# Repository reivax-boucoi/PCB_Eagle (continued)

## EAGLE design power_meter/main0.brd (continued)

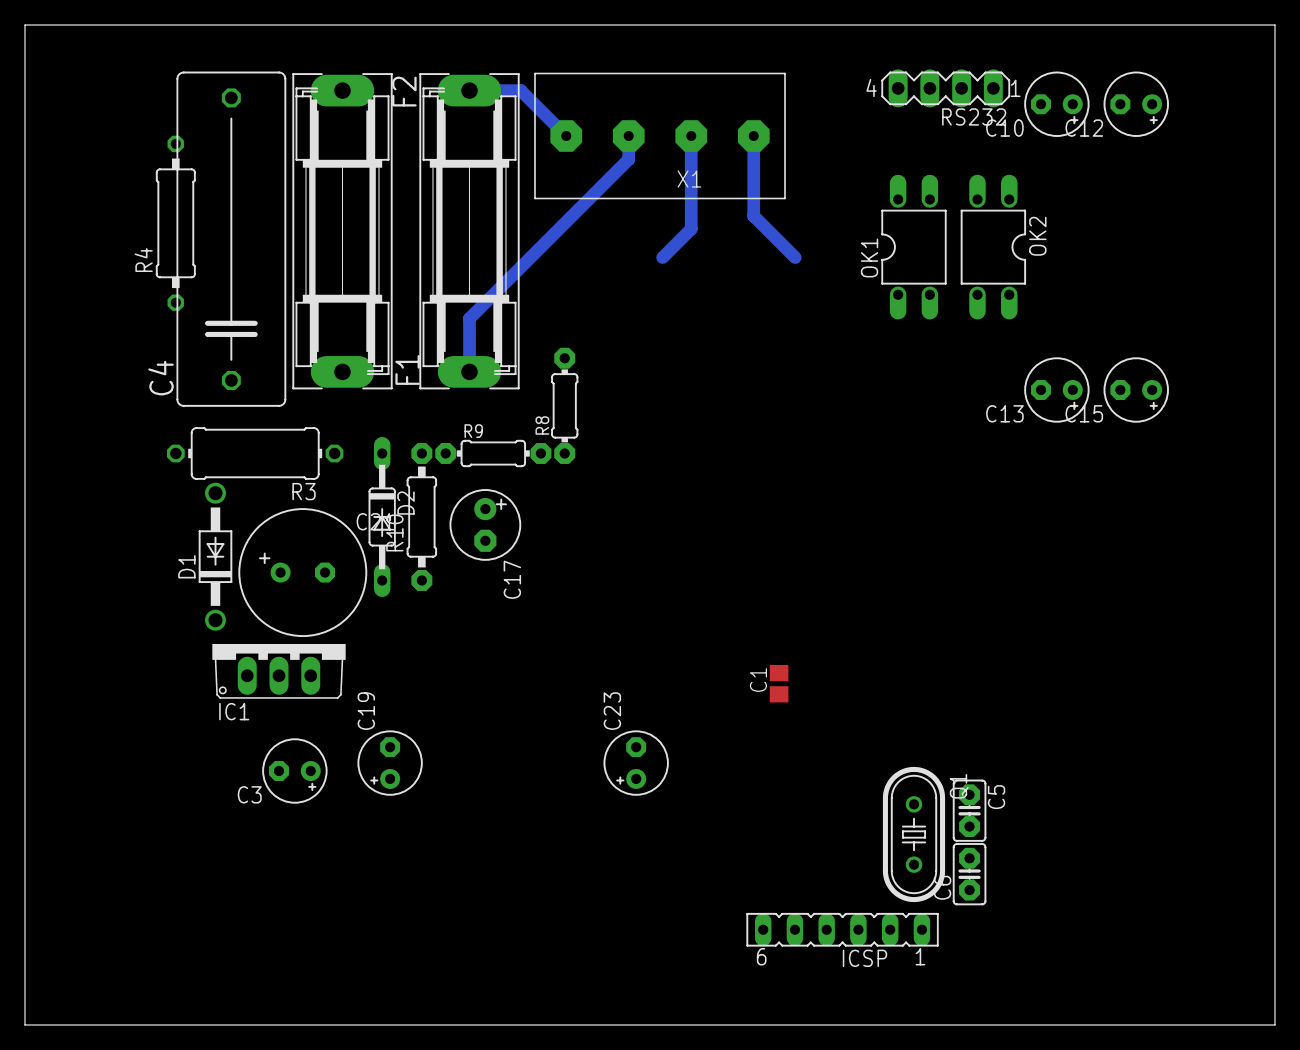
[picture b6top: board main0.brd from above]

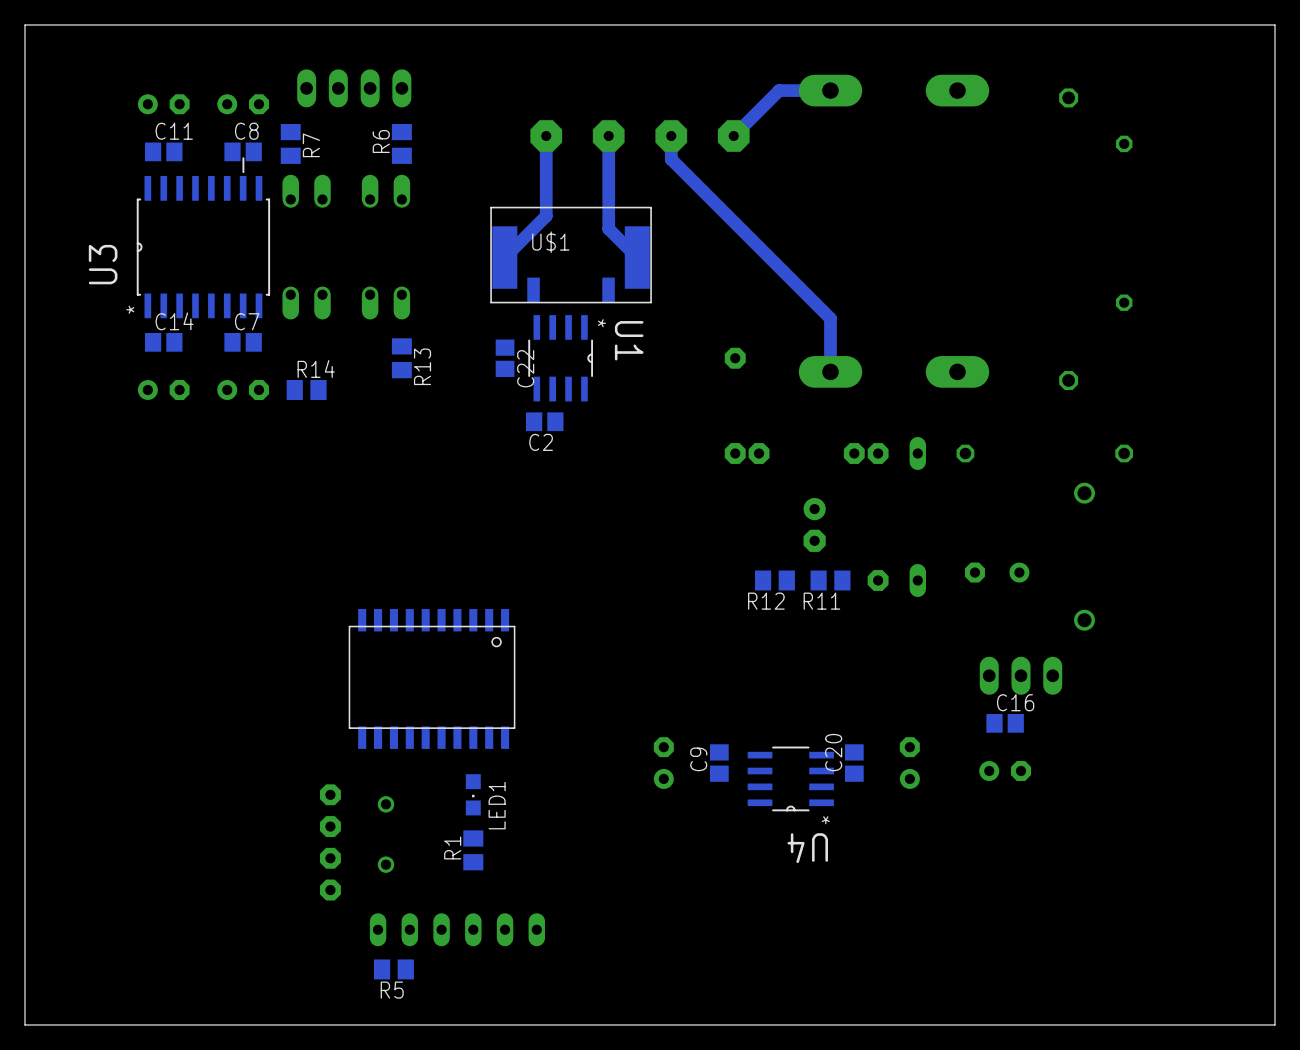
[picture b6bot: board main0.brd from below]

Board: 2 copper layers, 100.0 x 80.0 mm, 52 parts (23 on the bottom side), 32 nets.

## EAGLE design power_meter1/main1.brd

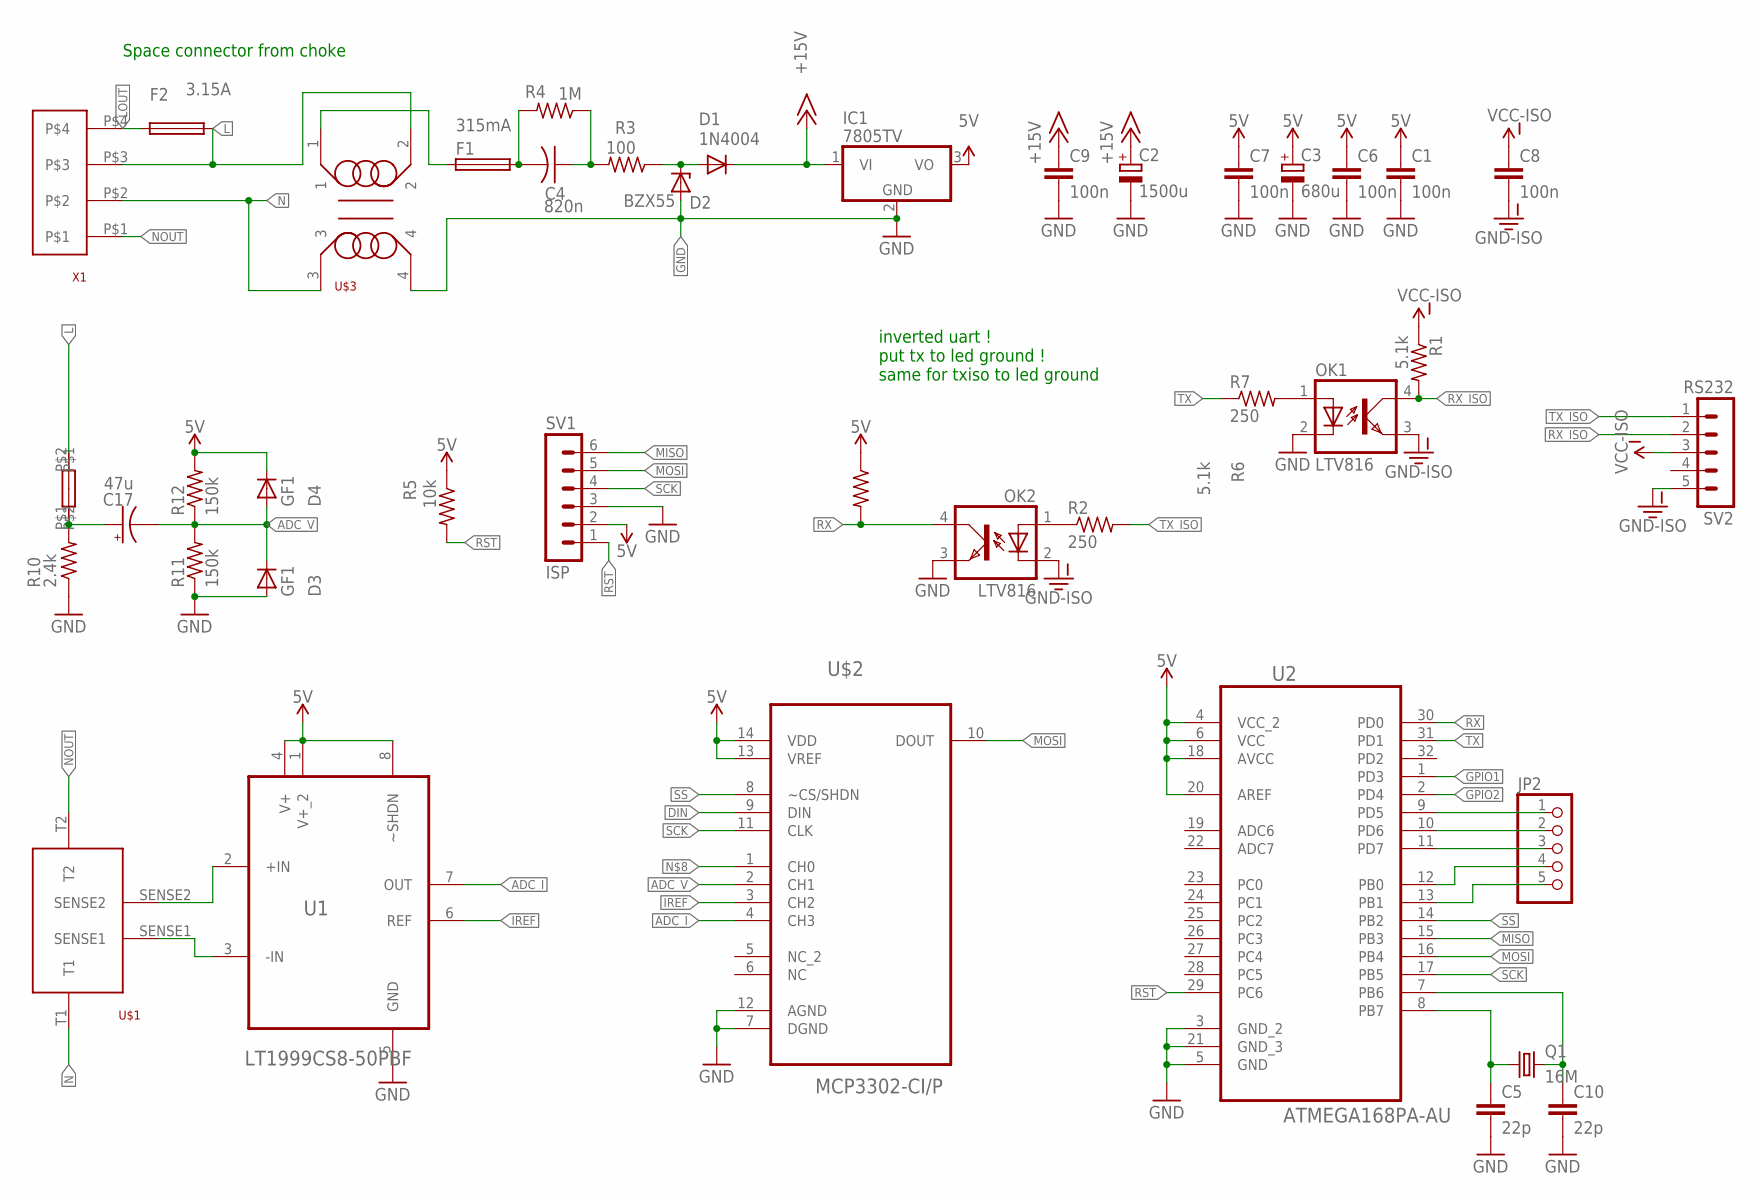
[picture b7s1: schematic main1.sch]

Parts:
C1, C6, C7, C9: 100n; C0603K
C2: 1500u; E5-10,5
C3: 680u; E3,5-8
C4: 820n; C225-087X268
C5, C10: 22p; C0603
C8: 100n; C0603
C17: 47u; E5-6
D1: 1N4004; DO41-10
D2: BZX55; DO35Z10
D3, D4: GF1; SMA-DO214AC
F1: 315mA; SH22,5
F2: 3.15A; SH22,5
IC1: 7805TV; TO220V
JP2: PINHD-1X5; 1X05
OK1, OK2: LTV816; DIL04
Q1: 16M; HC49U-V
R1: 5.1k; M0805
R2: 250; M0805
R3: 100; 0411/15
R4: 1M; 0617/17
R5: 10k; M0805
R6: 5.1k; R0603
R7: 250; R0603
R10: 2.4k; 0617/17
R11, R12: 150k; M0805
R13: 150k180k; RESISTOR_LONG
SV1: ISP; MA06-1
SV2: RS232; MA05-1
U1: LT1999CS8-50PBF; SOIC127P600X175-8N
U2: ATMEGA168PA-AU; QFP80P900X900X120-32N
U$1: CSR2TTE30L0F
U$2: MCP3302-CI/P; DIP254P762X533-14
U$3: B302L_CM_CHOKE
X1: SCREWTERM_5MM_4WAY

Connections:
5V: C1.1, C3.+, C6.1, C7.1, D4.K (C), IC1.3 (VO), R5.1, R6.1, R12.2, SV1.2, U1.1 (V+_2), U1.4 (V+), U1.8 (~SHDN), U2.4 (VCC_2), U2.6 (VCC), U2.18 (AVCC), U2.20 (AREF), U$2.13 (VREF), U$2.14 (VDD)
+15V: C2.+, C9.1, D1.C, IC1.1 (VI)
ADC_I: U1.7 (OUT), U$2.4 (CH3)
ADC_V: C17.-, D3.K (C), D4.A, R11.2, R12.1, U$2.2 (CH1)
DIN: U$2.9 (DIN)
GND: C1.2, C2.-, C3.-, C5.2, C6.2, C7.2, C9.2, C10.2, D2.A, D3.A, IC1.2 (GND), OK1.2 (C), OK2.3 (EMIT), R10.1, R11.1, SV1.3, U1.5 (GND), U2.3 (GND_2), U2.5 (GND), U2.21 (GND_3), U$2.7 (DGND), U$2.12 (AGND), U$3.4
GND-ISO: C8.2, OK1.3 (EMIT), OK2.2 (C), SV2.5
GPIO1: U2.1 (PD3)
GPIO2: U2.2 (PD4)
IREF: U1.6 (REF), U$2.3 (CH2)
L: F2.2, R13.P$2, U$3.2, X1.P$3
LOUT: F2.1, X1.P$4
MISO: SV1.6, U2.15 (PB3)
MOSI: SV1.5, U2.16 (PB4), U$2.10 (DOUT)
N: U$1.T1, U$3.3, X1.P$2
unnamed: C4.1, R3.2, R4.1
unnamed: C4.2, F1.2, R4.2
unnamed: D1.A, D2.C, R3.1
unnamed: U1.2 (+IN), U$1.SENSE2
unnamed: U1.3 (-IN), U$1.SENSE1
unnamed: F1.1, U$3.1
unnamed: OK1.1 (A), R7.2
unnamed: C5.1, Q1.1, U2.8 (PB7)
unnamed: C10.1, Q1.2, U2.7 (PB6)
unnamed: OK2.1 (A), R2.1
unnamed: JP2.1, U2.9 (PD5)
unnamed: JP2.2, U2.10 (PD6)
unnamed: JP2.3, U2.11 (PD7)
unnamed: JP2.4, U2.12 (PB0)
unnamed: JP2.5, U2.13 (PB1)
unnamed: C17.+, R10.2, R13.P$1
NOUT: U$1.T2, X1.P$1
RST: R5.2, SV1.1, U2.29 (PC6)
RX: OK2.4 (COL), R6.2, U2.30 (PD0)
RX_ISO: OK1.4 (COL), R1.2, SV2.2
SCK: SV1.4, U2.17 (PB5), U$2.11 (CLK)
SS: U2.14 (PB2), U$2.8 (~CS/SHDN)
TX: R7.1, U2.31 (PD1)
TX_ISO: R2.2, SV2.1
VCC-ISO: C8.1, R1.1, SV2.3

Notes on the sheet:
Space connector from choke
inverted uart ! put tx to led ground ! same for txiso to led ground

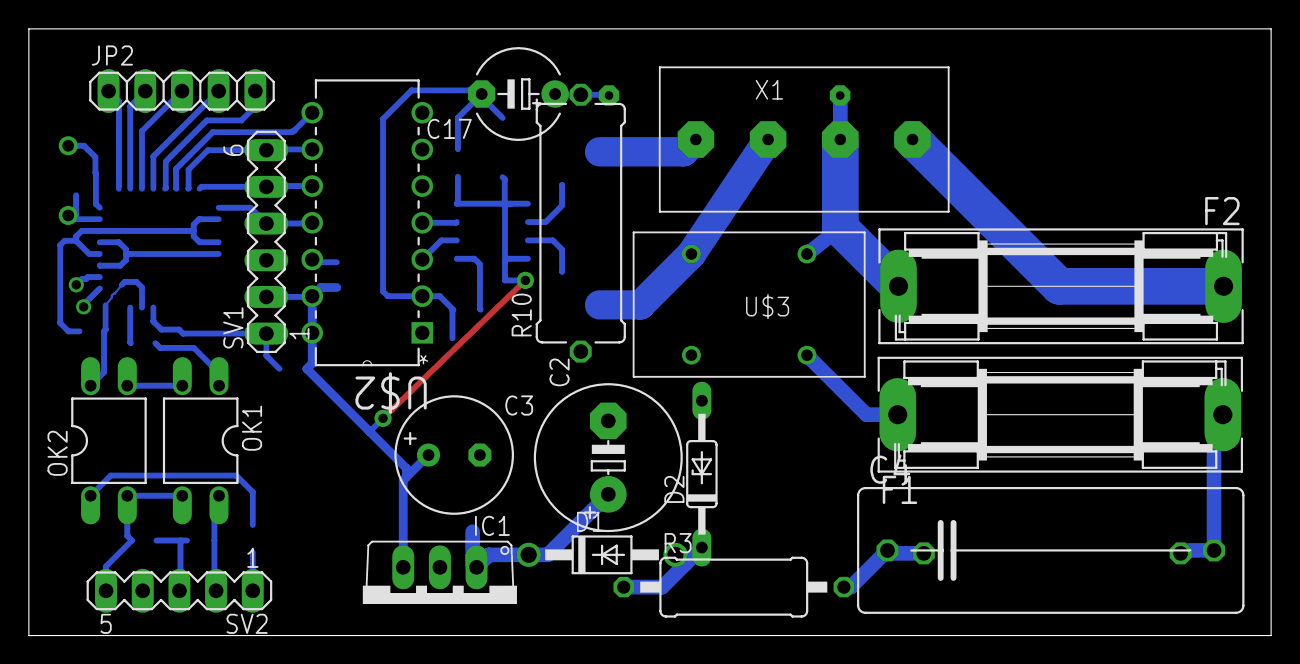
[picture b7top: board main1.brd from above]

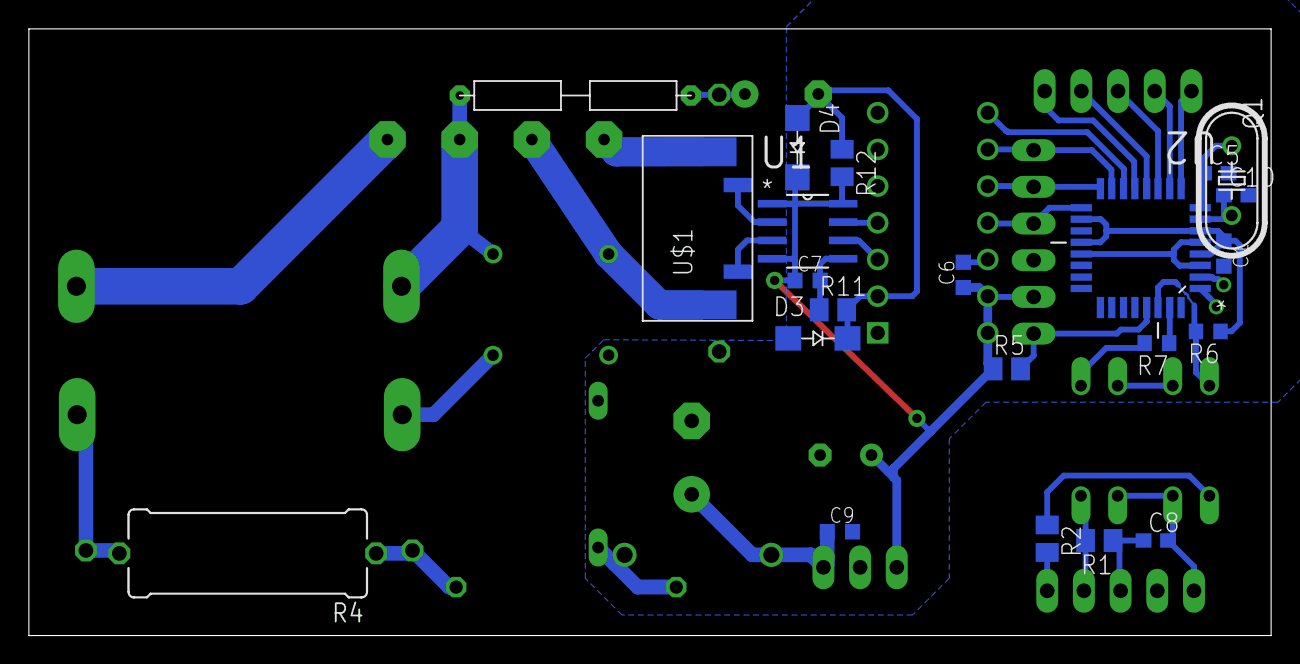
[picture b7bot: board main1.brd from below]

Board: 2 copper layers, 86.0 x 42.0 mm, 41 parts (22 on the bottom side), 37 nets.
